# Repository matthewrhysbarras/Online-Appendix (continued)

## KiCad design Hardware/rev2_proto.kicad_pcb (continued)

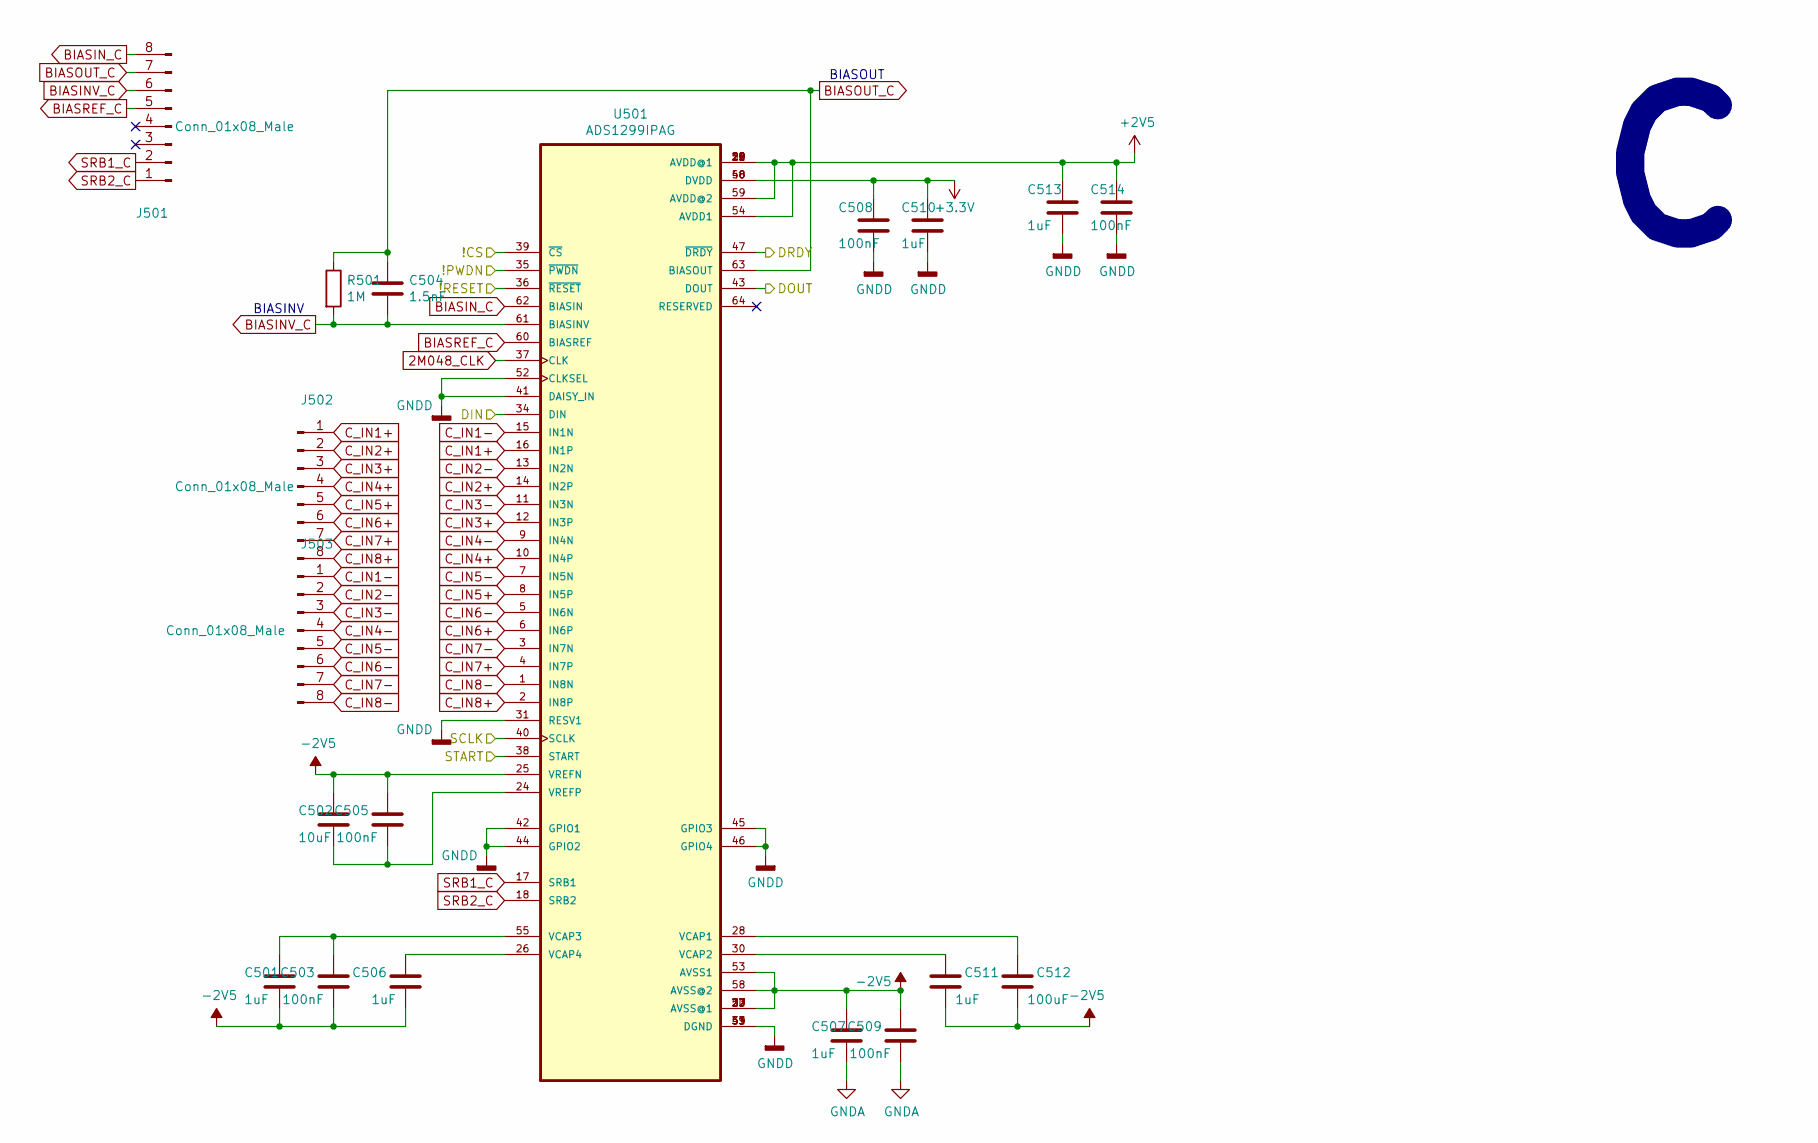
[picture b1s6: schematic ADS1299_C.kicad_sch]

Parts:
C501, C506, C507, C510, C511, C513: 1uF; C_0805_2012Metric
C502: 10uF; C_0805_2012Metric
C503, C505, C508, C509, C514: 100nF; C_0805_2012Metric
C504: 1.5nF; C_0805_2012Metric
C512: 100uF; C_0805_2012Metric
J501, J502, J503: Conn_01x08_Male; PinHeader_1x08_P2.54mm_Vertical
R501: 1M; R_0805_2012Metric
U501: ADS1299IPAG; QFP50P1200X1200X120-64N

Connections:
2M048_CLK: U501.37 (CLK); also elsewhere on the board
+2V5: C513.1, C514.1, U501.19 (AVDD@1), U501.21 (AVDD@1), U501.22 (AVDD@1), U501.54 (AVDD1), U501.56 (AVDD@1), U501.59 (AVDD@2); also elsewhere on the board
-2V5: C501.2, C502.1, C503.2, C505.1, C506.2, C507.1, C509.1, C511.2, C512.2, U501.20 (AVSS@1), U501.23 (AVSS@1), U501.25 (VREFN), U501.32 (AVSS@1), U501.53 (AVSS1), U501.57 (AVSS@1), U501.58 (AVSS@2); also elsewhere on the board
ADS_CS_3: U501.39 (~CS); also elsewhere on the board
BIASINV_C: C504.2, J501.6, R501.2, U501.61 (BIASINV)
BIASIN_C: J501.8, U501.62 (BIASIN)
BIASOUT_C: C504.1, J501.7, R501.1, U501.63 (BIASOUT)
BIASREF_C: J501.5, U501.60 (BIASREF)
C_IN1+: J502.1, U501.16 (IN1P)
C_IN1-: J503.1, U501.15 (IN1N)
C_IN2+: J502.2, U501.14 (IN2P)
C_IN2-: J503.2, U501.13 (IN2N)
C_IN3+: J502.3, U501.12 (IN3P)
C_IN3-: J503.3, U501.11 (IN3N)
C_IN4+: J502.4, U501.10 (IN4P)
C_IN4-: J503.4, U501.9 (IN4N)
C_IN5+: J502.5, U501.8 (IN5P)
C_IN5-: J503.5, U501.7 (IN5N)
C_IN6+: J502.6, U501.6 (IN6P)
C_IN6-: J503.6, U501.5 (IN6N)
C_IN7+: J502.7, U501.4 (IN7P)
C_IN7-: J503.7, U501.3 (IN7N)
C_IN8+: J502.8, U501.2 (IN8P)
C_IN8-: J503.8, U501.1 (IN8N)
GNDA: C507.2, C508.2, C509.2, C510.2, C513.2, C514.2, U501.31 (RESV1), U501.33 (DGND), U501.41 (DAISY_IN), U501.42 (GPIO1), U501.44 (GPIO2), U501.45 (GPIO3), U501.46 (GPIO4), U501.49 (DGND), U501.51 (DGND), U501.52 (CLKSEL); also elsewhere on the board
unnamed: C501.1, C503.1, U501.55 (VCAP3)
unnamed: C502.2, C505.2, U501.24 (VREFP)
unnamed: C506.1, U501.26 (VCAP4)
unnamed: C511.1, U501.30 (VCAP2)
unnamed: C512.1, U501.28 (VCAP1)
PB0: U501.36 (~RESET); also elsewhere on the board
PB1: U501.35 (~PWDN); also elsewhere on the board
PC5: U501.38 (START); also elsewhere on the board
PE8: U501.47 (~DRDY); also elsewhere on the board
SPI1_MISO: U501.43 (DOUT); also elsewhere on the board
SPI1_MOSI: U501.34 (DIN); also elsewhere on the board
SPI1_SCK: U501.40 (SCLK); also elsewhere on the board
SRB1_C: J501.2, U501.17 (SRB1)
SRB2_C: J501.1, U501.18 (SRB2)

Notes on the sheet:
BIASOUT
BIASINV

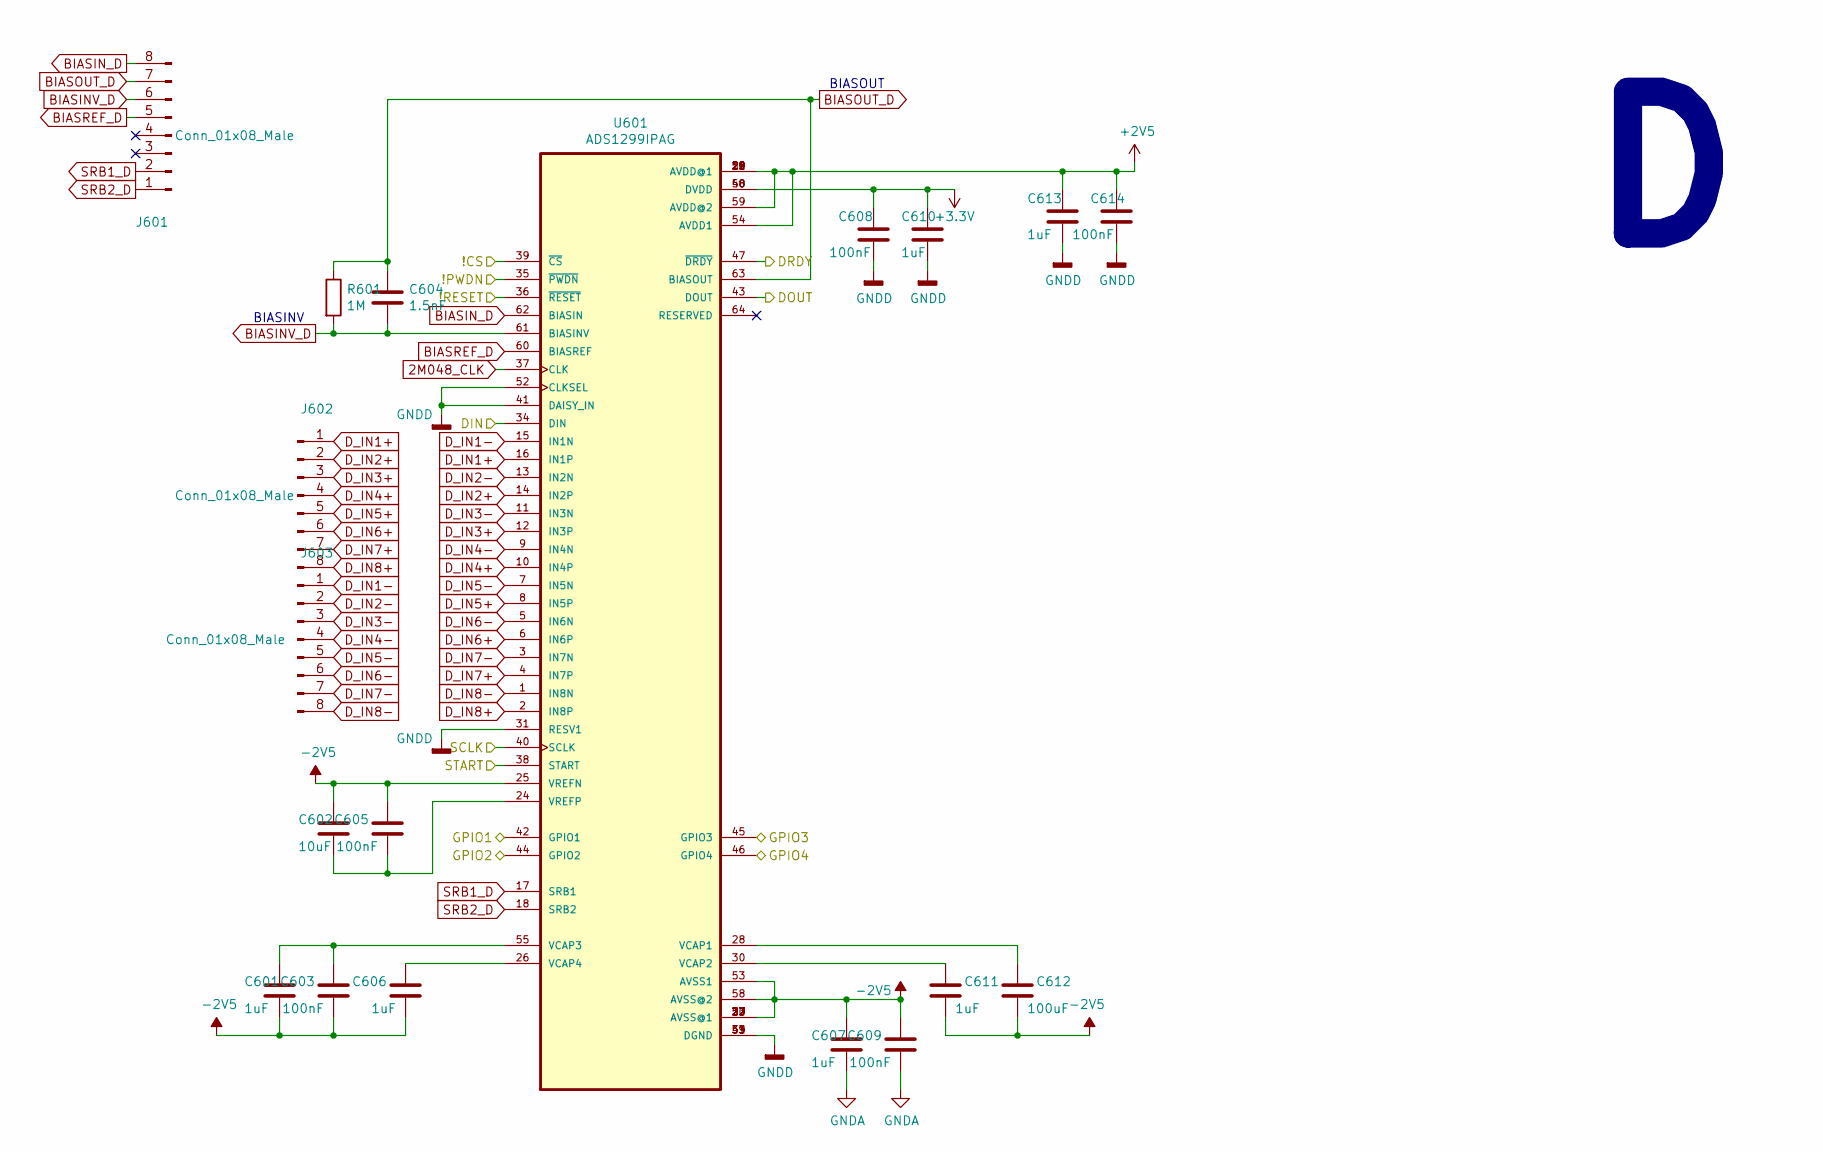
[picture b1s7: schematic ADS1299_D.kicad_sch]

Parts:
C601, C606, C607, C610, C611, C613: 1uF; C_0805_2012Metric
C602: 10uF; C_0805_2012Metric
C603, C605, C608, C609, C614: 100nF; C_0805_2012Metric
C604: 1.5nF; C_0805_2012Metric
C612: 100uF; C_0805_2012Metric
J601, J602, J603: Conn_01x08_Male; PinHeader_1x08_P2.54mm_Vertical
R601: 1M; R_0805_2012Metric
U601: ADS1299IPAG; QFP50P1200X1200X120-64N

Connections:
2M048_CLK: U601.37 (CLK); also elsewhere on the board
+2V5: C613.1, C614.1, U601.19 (AVDD@1), U601.21 (AVDD@1), U601.22 (AVDD@1), U601.54 (AVDD1), U601.56 (AVDD@1), U601.59 (AVDD@2); also elsewhere on the board
-2V5: C601.2, C602.1, C603.2, C605.1, C606.2, C607.1, C609.1, C611.2, C612.2, U601.20 (AVSS@1), U601.23 (AVSS@1), U601.25 (VREFN), U601.32 (AVSS@1), U601.53 (AVSS1), U601.57 (AVSS@1), U601.58 (AVSS@2); also elsewhere on the board
ADS_CS_4: U601.39 (~CS); also elsewhere on the board
BIASINV_D: C604.2, J601.6, R601.2, U601.61 (BIASINV)
BIASIN_D: J601.8, U601.62 (BIASIN)
BIASOUT_D: C604.1, J601.7, R601.1, U601.63 (BIASOUT)
BIASREF_D: J601.5, U601.60 (BIASREF)
D_IN1+: J602.1, U601.16 (IN1P)
D_IN1-: J603.1, U601.15 (IN1N)
D_IN2+: J602.2, U601.14 (IN2P)
D_IN2-: J603.2, U601.13 (IN2N)
D_IN3+: J602.3, U601.12 (IN3P)
D_IN3-: J603.3, U601.11 (IN3N)
D_IN4+: J602.4, U601.10 (IN4P)
D_IN4-: J603.4, U601.9 (IN4N)
D_IN5+: J602.5, U601.8 (IN5P)
D_IN5-: J603.5, U601.7 (IN5N)
D_IN6+: J602.6, U601.6 (IN6P)
D_IN6-: J603.6, U601.5 (IN6N)
D_IN7+: J602.7, U601.4 (IN7P)
D_IN7-: J603.7, U601.3 (IN7N)
D_IN8+: J602.8, U601.2 (IN8P)
D_IN8-: J603.8, U601.1 (IN8N)
GNDA: C607.2, C608.2, C609.2, C610.2, C613.2, C614.2, U601.31 (RESV1), U601.33 (DGND), U601.41 (DAISY_IN), U601.49 (DGND), U601.51 (DGND), U601.52 (CLKSEL); also elsewhere on the board
unnamed: C601.1, C603.1, U601.55 (VCAP3)
unnamed: C602.2, C605.2, U601.24 (VREFP)
unnamed: C606.1, U601.26 (VCAP4)
unnamed: C611.1, U601.30 (VCAP2)
unnamed: C612.1, U601.28 (VCAP1)
PB0: U601.36 (~RESET); also elsewhere on the board
PB1: U601.35 (~PWDN); also elsewhere on the board
PB11: U601.44 (GPIO2); also elsewhere on the board
PB12: U601.45 (GPIO3); also elsewhere on the board
PB13: U601.46 (GPIO4); also elsewhere on the board
PC5: U601.38 (START); also elsewhere on the board
PD9: U601.42 (GPIO1); also elsewhere on the board
PE9: U601.47 (~DRDY); also elsewhere on the board
SPI1_MISO: U601.43 (DOUT); also elsewhere on the board
SPI1_MOSI: U601.34 (DIN); also elsewhere on the board
SPI1_SCK: U601.40 (SCLK); also elsewhere on the board
SRB1_D: J601.2, U601.17 (SRB1)
SRB2_D: J601.1, U601.18 (SRB2)

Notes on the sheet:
BIASOUT
BIASINV

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
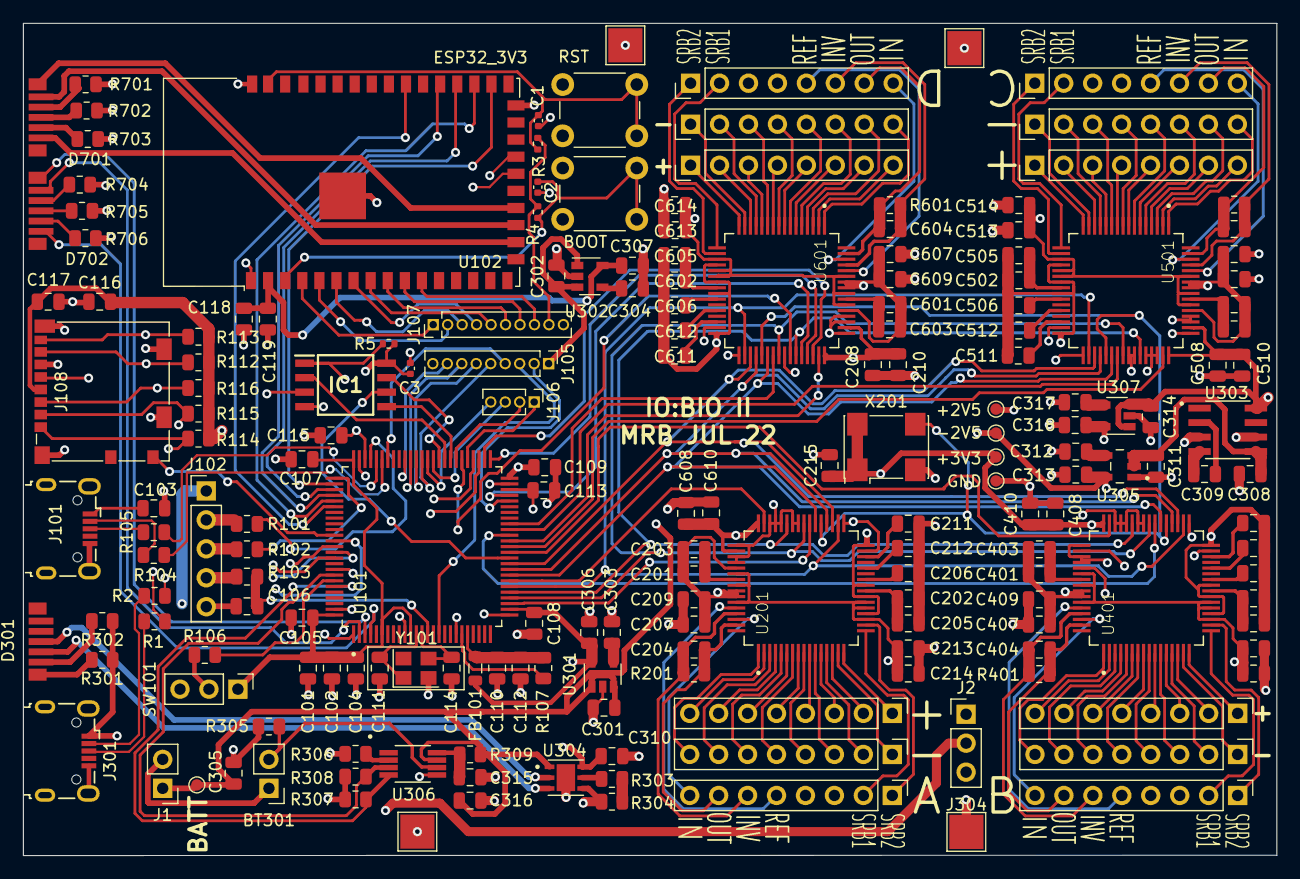
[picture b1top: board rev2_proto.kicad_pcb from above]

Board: 4 copper layers, 110.0 x 73.0 mm, 187 parts (0 on the bottom side), 226 nets.

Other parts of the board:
BOOT: SW_SPST; SW_PUSH_6mm_H4.3mm
J304#2, J304#3, J304#4: Conn_01x01_Male; TestPoint_Pad_3.0x3.0mm
RST: SW_SPST; SW_PUSH_6mm_H4.3mm

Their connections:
ESP32_BOOT: BOOT.1 (A); also elsewhere on the board
ESP32_RESET: RST.1 (A); also elsewhere on the board
GNDA: BOOT.2 (B), J304#2.1, J304#3.1, J304#4.1, RST.2 (B); also elsewhere on the board

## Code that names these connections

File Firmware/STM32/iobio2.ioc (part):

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Mcu.Name=STM32H743VITx
Mcu.Package=LQFP100
Mcu.UserName=STM32H743VITx
PA10.GPIOParameters=GPIO_Label
PA10.GPIO_Label=TLC5940_XERR
PA10.Signal=GPIO_Input
PA13\ (JTMS/SWDIO).Mode=Serial_Wire
PA13\ (JTMS/SWDIO).Signal=DEBUG_JTMS-SWDIO
PA14\ (JTCK/SWCLK).Mode=Serial_Wire
PA14\ (JTCK/SWCLK).Signal=DEBUG_JTCK-SWCLK
PA15\ (JTDI).Mode=NSS_Signal_Hard_Output
PA15\ (JTDI).Signal=SPI3_NSS
PA2.Mode=Asynchronous
PA2.Signal=USART2_TX
PA3.Mode=Asynchronous
PA3.Signal=USART2_RX
PA4.GPIOParameters=PinState,GPIO_Label
PA4.GPIO_Label=ADS1_CS
PA4.PinState=GPIO_PIN_RESET
PA4.Signal=GPIO_Output
PA5.Mode=Full_Duplex_Master
PA5.Signal=SPI1_SCK
PA6.Mode=Full_Duplex_Master
PA6.Signal=SPI1_MISO
PA7.Mode=Full_Duplex_Master
PA7.Signal=SPI1_MOSI
PB0.GPIOParameters=PinState,GPIO_Label
PB0.GPIO_Label=ADS1_RESET
PB0.PinState=GPIO_PIN_RESET
PB0.Signal=GPIO_Output
PB1.GPIOParameters=PinState,GPIO_Label
PB1.GPIO_Label=ADS1_PWDN
PB1.PinState=GPIO_PIN_RESET
PB1.Signal=GPIO_Output
PB10.Mode=Full_Duplex_Master
PB10.Signal=SPI2_SCK
PC1.GPIOParameters=GPIO_PuPd
PC1.GPIO_PuPd=GPIO_PULLUP
PC1.Mode=Full_Duplex_Master
PC1.Signal=SPI2_MOSI
PC10.Mode=Full_Duplex_Master
PC10.Signal=SPI3_SCK
PC11.GPIOParameters=GPIO_PuPd
PC11.GPIO_PuPd=GPIO_NOPULL
PC11.Mode=Full_Duplex_Master
PC11.Signal=SPI3_MISO
PC12.Mode=Full_Duplex_Master
PC12.Signal=SPI3_MOSI
PC2_C.Mode=Full_Duplex_Master
PC2_C.Signal=SPI2_MISO
PC4.GPIOParameters=GPIO_Label,GPIO_ModeDefaultEXTI
PC4.GPIO_Label=ADS1_DRDY
PC4.GPIO_ModeDefaultEXTI=GPIO_MODE_IT_FALLING
PC4.Signal=GPXTI4
PC5.GPIOParameters=PinState,GPIO_Label
PC5.GPIO_Label=ADS1_START
PC5.PinState=GPIO_PIN_RESET
PC5.Signal=GPIO_Output
PC6.GPIOParameters=GPIO_Speed,PinState,GPIO_Label
PC6.GPIO_Label=TLC5940_BLANK
PC6.GPIO_Speed=GPIO_SPEED_FREQ_VERY_HIGH
PC6.PinState=GPIO_PIN_SET
PC6.Signal=GPIO_Output
PC7.GPIOParameters=GPIO_Speed,GPIO_Label
PC7.GPIO_Label=TLC5940_GSCLK
PC7.GPIO_Speed=GPIO_SPEED_FREQ_VERY_HIGH
PC7.Signal=GPIO_Output
PC8.GPIOParameters=GPIO_Speed,GPIO_Label
PC8.GPIO_Label=TLC5940_VPRG
PC8.GPIO_Speed=GPIO_SPEED_FREQ_VERY_HIGH
PC8.Signal=GPIO_Output
PC9.GPIOParameters=GPIO_Speed,GPIO_Label
PC9.GPIO_Label=TLC5940_XLAT
PC9.GPIO_Speed=GPIO_SPEED_FREQ_VERY_HIGH
PC9.Signal=GPIO_Output
PD15.Signal=GPIO_Output
PD8.GPIOParameters=GPIO_PuPd,GPIO_Label,GPIO_ModeDefaultEXTI
PD8.GPIO_Label=ESP32_DRDY
PD8.GPIO_ModeDefaultEXTI=GPIO_MODE_IT_RISING
PD8.GPIO_PuPd=GPIO_NOPULL
PD8.Signal=GPXTI8
PE0.GPIOParameters=GPIO_Speed,PinState,GPIO_PuPd,GPIO_ModeDefaultOutputPP
PE0.GPIO_ModeDefaultOutputPP=GPIO_MODE_OUTPUT_PP
PE0.GPIO_PuPd=GPIO_NOPULL
PE0.GPIO_Speed=GPIO_SPEED_FREQ_LOW
PE0.PinState=GPIO_PIN_RESET
PE0.Signal=GPIO_Output
PE1.GPIOParameters=GPIO_Speed,PinState,GPIO_PuPd,GPIO_ModeDefaultOutputPP
PE1.GPIO_ModeDefaultOutputPP=GPIO_MODE_OUTPUT_PP
PE1.GPIO_PuPd=GPIO_NOPULL
PE1.GPIO_Speed=GPIO_SPEED_FREQ_LOW
PE1.PinState=GPIO_PIN_RESET
PE1.Signal=GPIO_Output
PE10.GPIOParameters=PinState,GPIO_Label
PE10.GPIO_Label=ADS4_CS
PE10.PinState=GPIO_PIN_RESET
PE10.Signal=GPIO_Output
PE11.GPIOParameters=PinState,GPIO_Label
PE11.GPIO_Label=ADS3_CS
PE11.PinState=GPIO_PIN_RESET
PE11.Signal=GPIO_Output
PE12.GPIOParameters=PinState,GPIO_Label
PE12.GPIO_Label=ADS2_CS
PE12.PinState=GPIO_PIN_RESET
PE12.Signal=GPIO_Output
PE2.GPIOParameters=GPIO_PuPd,GPIO_Label
PE2.GPIO_Label=LED_B
PE2.GPIO_PuPd=GPIO_NOPULL
PE2.Signal=GPIO_Output
PE3.GPIOParameters=GPIO_Label
PE3.GPIO_Label=LED_G
PE3.Signal=GPIO_Output
PE4.GPIOParameters=GPIO_Label
PE4.GPIO_Label=LED_R
PE4.Signal=GPIO_Output
RCC.SYSCLKFreq_VALUE=480000000
RCC.SYSCLKSource=RCC_SYSCLKSOURCE_PLLCLK
board=custom
